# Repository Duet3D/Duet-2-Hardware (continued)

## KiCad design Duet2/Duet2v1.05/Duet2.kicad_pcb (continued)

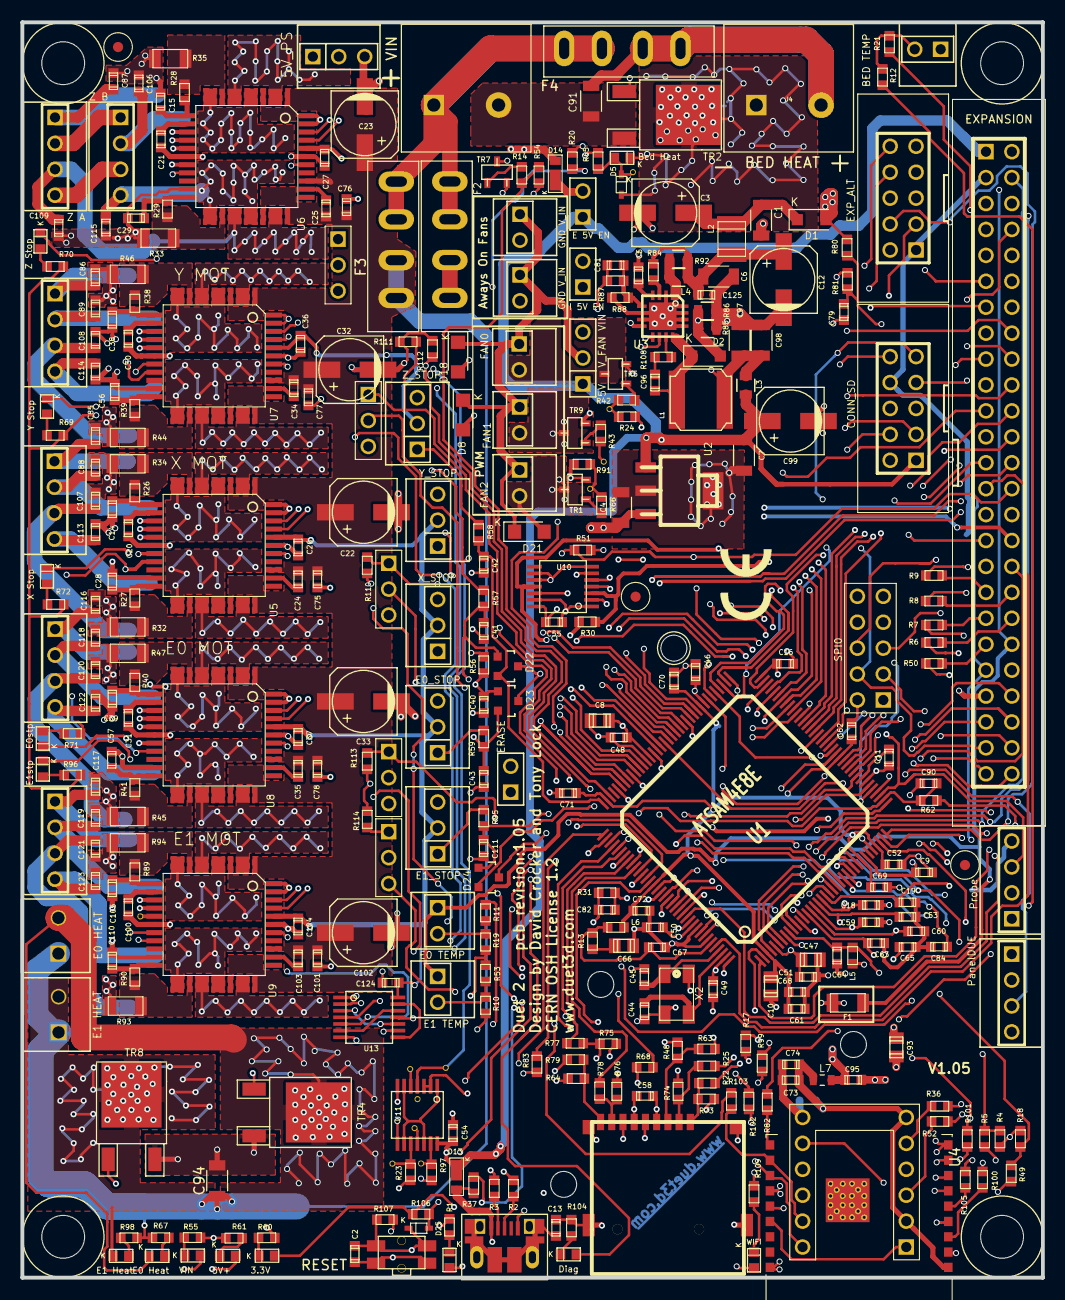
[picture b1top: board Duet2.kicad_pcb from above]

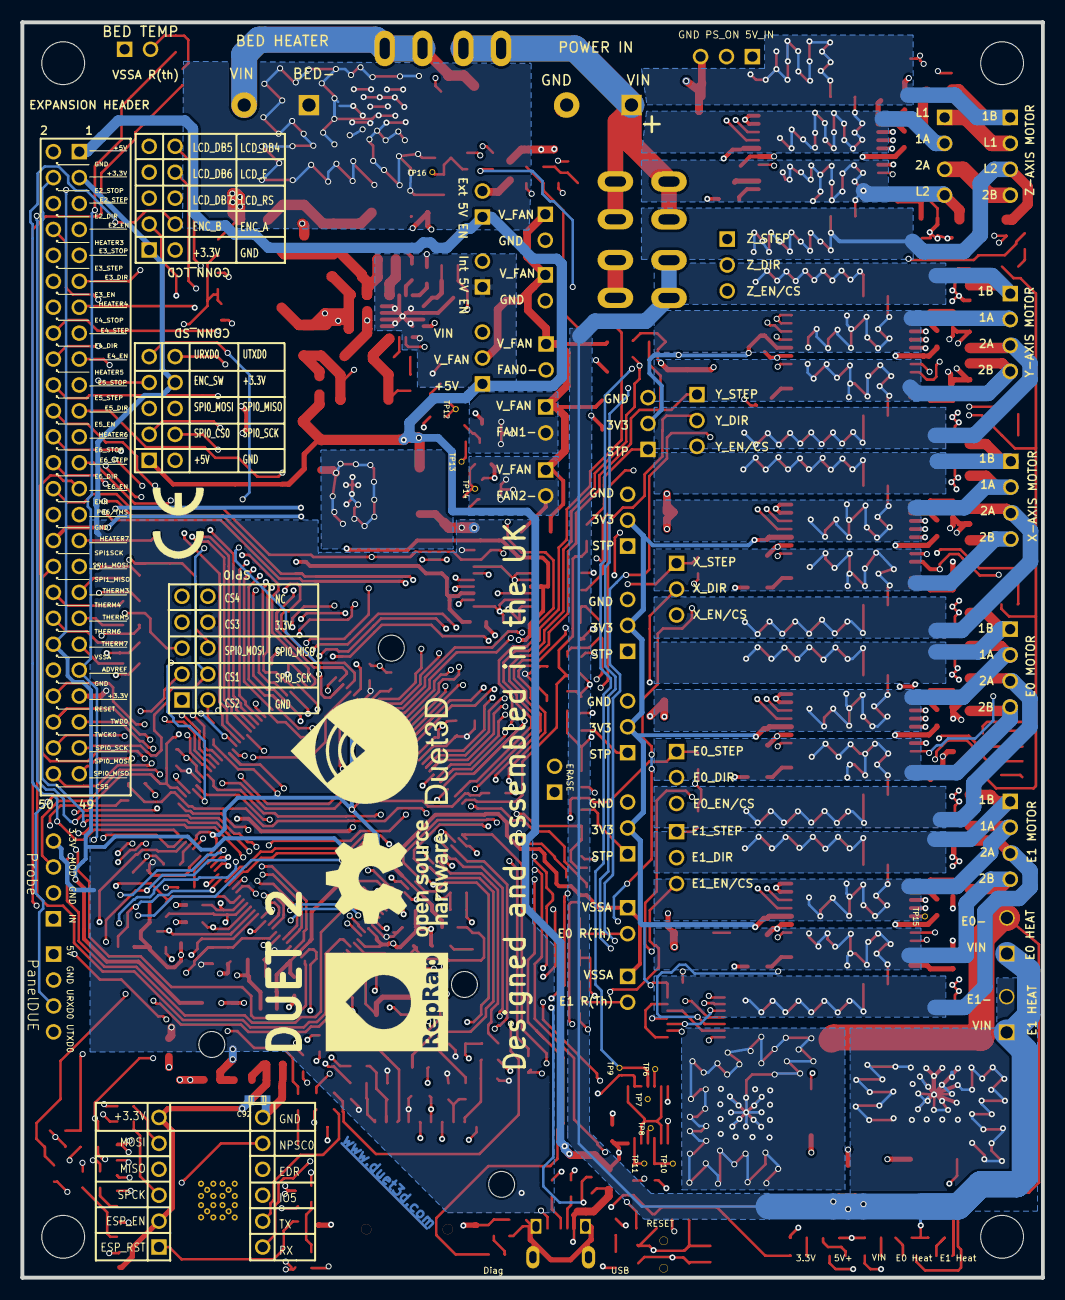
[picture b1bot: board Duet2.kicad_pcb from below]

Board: 4 copper layers, 100.0 x 123.0 mm, 356 parts (5 on the bottom side), 281 nets.

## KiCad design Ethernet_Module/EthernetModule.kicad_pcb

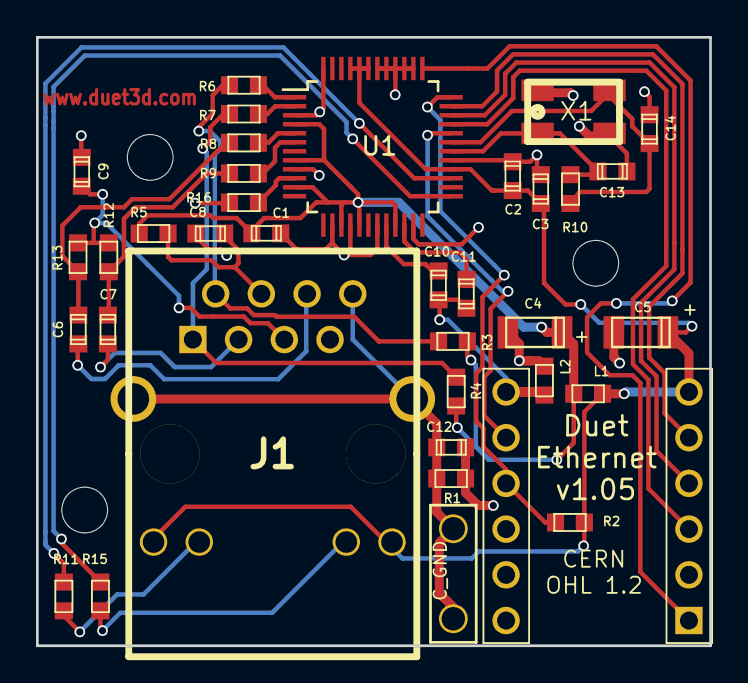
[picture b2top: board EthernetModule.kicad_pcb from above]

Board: 2 copper layers, 37.4 x 33.8 mm, 36 parts (0 on the bottom side), 32 nets.

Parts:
C1, C2, C3: 0u1; C_0603
C4, C5: 10uF/16V; C_1206_pol
C6, C7: 6n8; C_0603
C8: 22n; C_0603
C9, C11: 10n; C_0603
C10: 4u7; C_0603
C12: 0u01 +200V; C_0603
C13, C14: 18p; C_0603
J1: RJ45+MAG
J2: CONN_ALT_HEADER; CONN_ALT_HEADER_th
J3: C_GND; 2.8mm_Spade_terminal
L1, L2: L_MINI; R_0603
R1, R10: 1M; R_0603
R2: 4K7; R_0603
R3, R4, R12, R13: 49R9; R_0603
R5: 10R; R_0603
R6, R7, R8, R9: 33R; R_0603
R11, R15: 220R; R_0603
R16: 12K4; R_0603
U1: W5500; LQFP-48_7x7mm_Pitch0.5mm
X1: CRYSTAL_4PIN; Xtal_5x3.2

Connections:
+3V3: C2.1, C3.1, C5.1, J1.9, J1.12, J2.6, L1.2, R2.2, U1.28, U1.43, U1.44, U1.45
+3V3_A: C1.1, C4.1, L1.1, R3.2, R4.2, R5.2, U1.4, U1.8, U1.11, U1.15, U1.17, U1.21
ACTLED: R11.2, U1.27
AGND: C1.2, C4.2, C8.2, C9.2, L2.1, R16.1, U1.3, U1.9, U1.14, U1.16, U1.19, U1.48
GND: C2.2, C3.2, C5.2, C10.2, C11.2, C12.1, C13.2, C14.2, J2.10, J2.15, L2.2, R1.1, U1.23, U1.29, U1.38, U1.39, U1.40, U1.41, U1.42, X1.2, X1.4
INTn: J2.12, R2.1, U1.36
LINKLED: R15.2, U1.25
MISO: J2.4, U1.34
MOSI: J2.5, U1.35
unnamed: C6.1, R8.1, R13.2
unnamed: C6.2, J1.6
unnamed: C7.1, R9.1, R12.2
unnamed: C7.2, J1.3
unnamed: C8.1, J1.4, R5.1
unnamed: C9.1, J1.5, R12.1, R13.1
unnamed: C10.1, U1.20
unnamed: C11.1, U1.22
unnamed: C12.2, J1.8, J1.13, J1.14, J3.1, R1.2
unnamed: C13.1, R10.2, U1.30, X1.1
unnamed: C14.1, R10.1, U1.31, X1.3
unnamed: J1.1, R4.1, R7.1
unnamed: J1.2, R3.1, R6.1
unnamed: J1.10, R11.1
unnamed: J1.11, R15.1
unnamed: R6.2, U1.1
unnamed: R7.2, U1.2
unnamed: R8.2, U1.5
unnamed: R9.2, U1.6
unnamed: R16.2, U1.10
RSTn: J2.1, U1.37
SCLK: J2.3, U1.33
SCSn: J2.11, U1.32

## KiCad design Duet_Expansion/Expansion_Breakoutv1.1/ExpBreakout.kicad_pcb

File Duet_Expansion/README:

For info on the Duex2/5 see:
https://duet3d.com/wiki/Duex2_and_Duex5_Features

For more info on the Duex4 expansion board see:
http://blog.think3dprint3d.com/2015/04/duex4-v02a-minor-updates.html

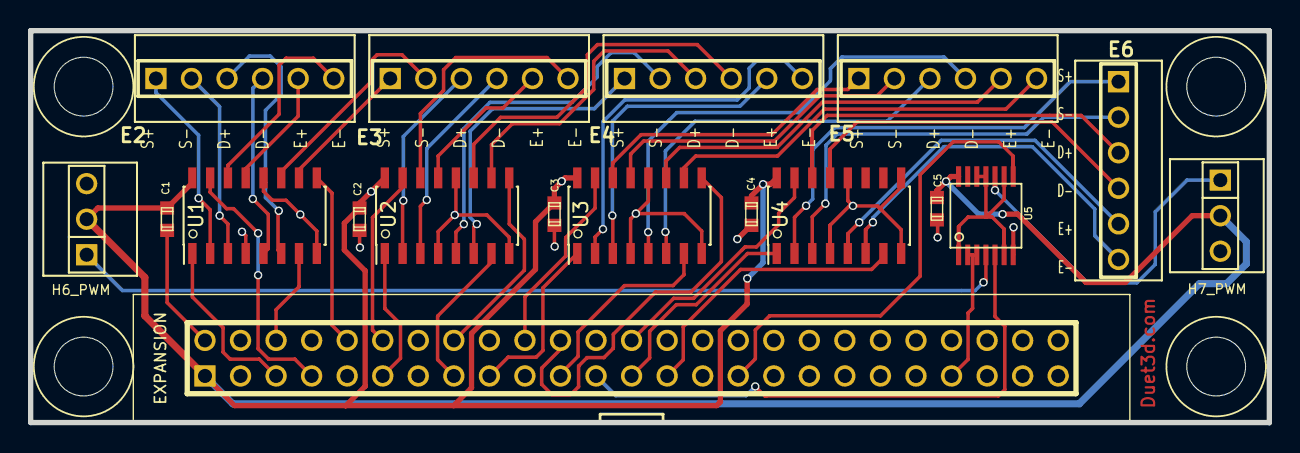
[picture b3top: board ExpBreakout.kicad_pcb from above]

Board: 2 copper layers, 88.5 x 28.0 mm, 22 parts (0 on the bottom side), 53 nets.

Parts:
C1, C2, C3, C4, C5: 0u1; C_0603
J1: EXPANSION; PIN_ARRAY_25X2
M4, M5, M6, M7: MOUNTING; Fixing_M4
P1: E2; PIN_ARRAY_6x1
P2: E3; PIN_ARRAY_6x1
P3: E4; PIN_ARRAY_6x1
P4: E5; PIN_ARRAY_6x1
P5: E6; PIN_ARRAY_6x1
P6: H6_PWM; PIN_ARRAY_3X1
P7: H7_PWM; PIN_ARRAY_3X1
U1, U2, U3, U4: 75ALS192; SOIC-16_3.9x9.9mm_Pitch1.27mm
U5: 74HCT02; TSSOP-14

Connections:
+3.3V: J1.3, J1.43, U5.2, U5.3
+5V: C1.1, C2.1, C3.1, C4.1, C5.1, J1.1, P6.2, P7.2, U1.16, U2.16, U3.16, U4.16, U5.14
E2_DIR: J1.6, U1.7
E2_D_OUT_Y: P1.3, U1.6
E2_D_OUT_Z: P1.4, U1.5
E2_EN: J1.7, U1.15
E2_E_OUT_Y: P1.6, U1.14
E2_E_OUT_Z: P1.5, U1.13
E2_STEP: J1.5, U1.1
E2_S_OUT_Y: P1.1, U1.2
E2_S_OUT_Z: P1.2, U1.3
E3_DIR: J1.11, U2.1
E3_D_OUT_Y: P2.3, U2.2
E3_D_OUT_Z: P2.4, U2.3
E3_EN: J1.12, U2.15
E3_E_OUT_Y: P2.6, U2.14
E3_E_OUT_Z: P2.5, U2.13
E3_STEP: J1.10, U1.9
E3_S_OUT_Y: P2.1, U1.10
E3_S_OUT_Z: P2.2, U1.11
E4_DIR: J1.16, U2.9
E4_D_OUT_Y: P3.3, U2.10
E4_D_OUT_Z: P3.4, U2.11
E4_EN: J1.17, U3.1
E4_E_OUT_Y: P3.6, U3.2
E4_E_OUT_Z: P3.5, U3.3
E4_STEP: J1.15, U2.7
E4_S_OUT_Y: P3.1, U2.6
E4_S_OUT_Z: P3.2, U2.5
E5_DIR: J1.21, U3.7
E5_D_OUT_Y: P4.3, U3.6
E5_D_OUT_Z: P4.4, U3.5
E5_EN: J1.22, U3.9
E5_E_OUT_Y: P4.6, U3.10
E5_E_OUT_Z: P4.5, U3.11
E5_STEP: J1.20, U3.15
E5_S_OUT_Y: P4.1, U3.14
E5_S_OUT_Z: P4.2, U3.13
E6_DIR: J1.26, U4.15
E6_D_OUT_Y: P5.3, U4.14
E6_D_OUT_Z: P5.4, U4.13
E6_EN: J1.27, U4.7
E6_E_OUT_Y: P5.6, U4.6
E6_E_OUT_Z: P5.5, U4.5
E6_STEP: J1.25, U4.1
E6_S_OUT_Y: P5.1, U4.2
E6_S_OUT_Z: P5.2, U4.3
GND: C1.2, C2.2, C3.2, C4.2, C5.2, J1.2, J1.30, J1.42, P6.3, P7.3, U1.4, U1.8, U1.12, U2.4, U2.8, U2.12, U3.4, U3.8, U3.12, U4.4, U4.8, U4.9, U4.12, U5.7
HEATER6: J1.23, U5.5
HEATER6_PWM: P6.1, U5.4
HEATER7: J1.31, U5.8
HEATER7_PWM: P7.1, U5.10
unnamed: U5.1, U5.6, U5.9, U5.11, U5.12

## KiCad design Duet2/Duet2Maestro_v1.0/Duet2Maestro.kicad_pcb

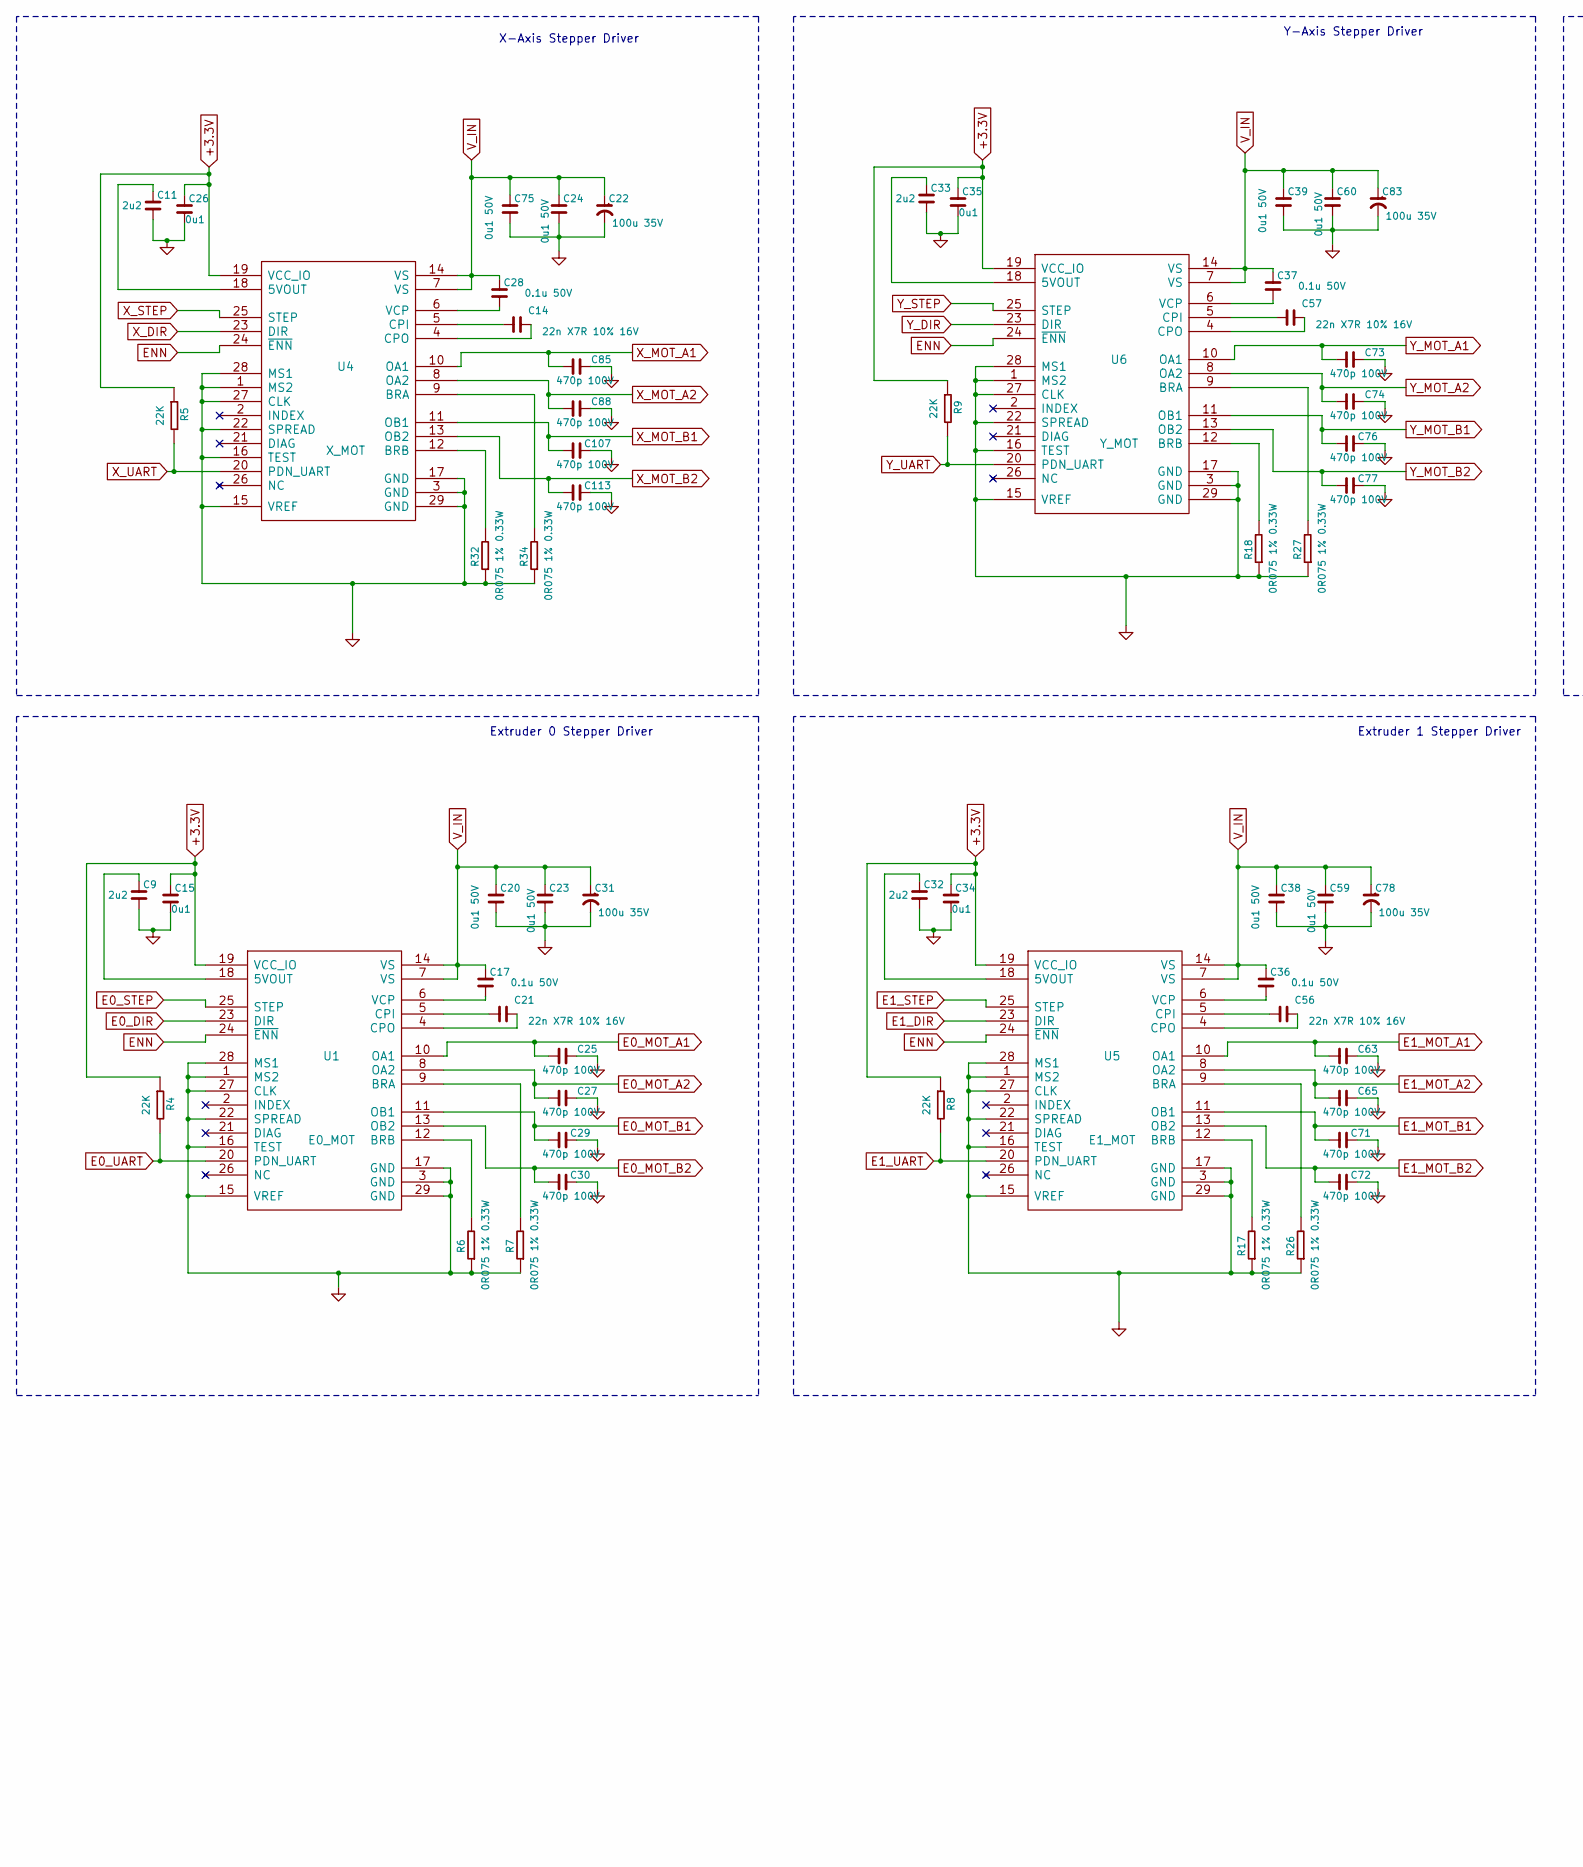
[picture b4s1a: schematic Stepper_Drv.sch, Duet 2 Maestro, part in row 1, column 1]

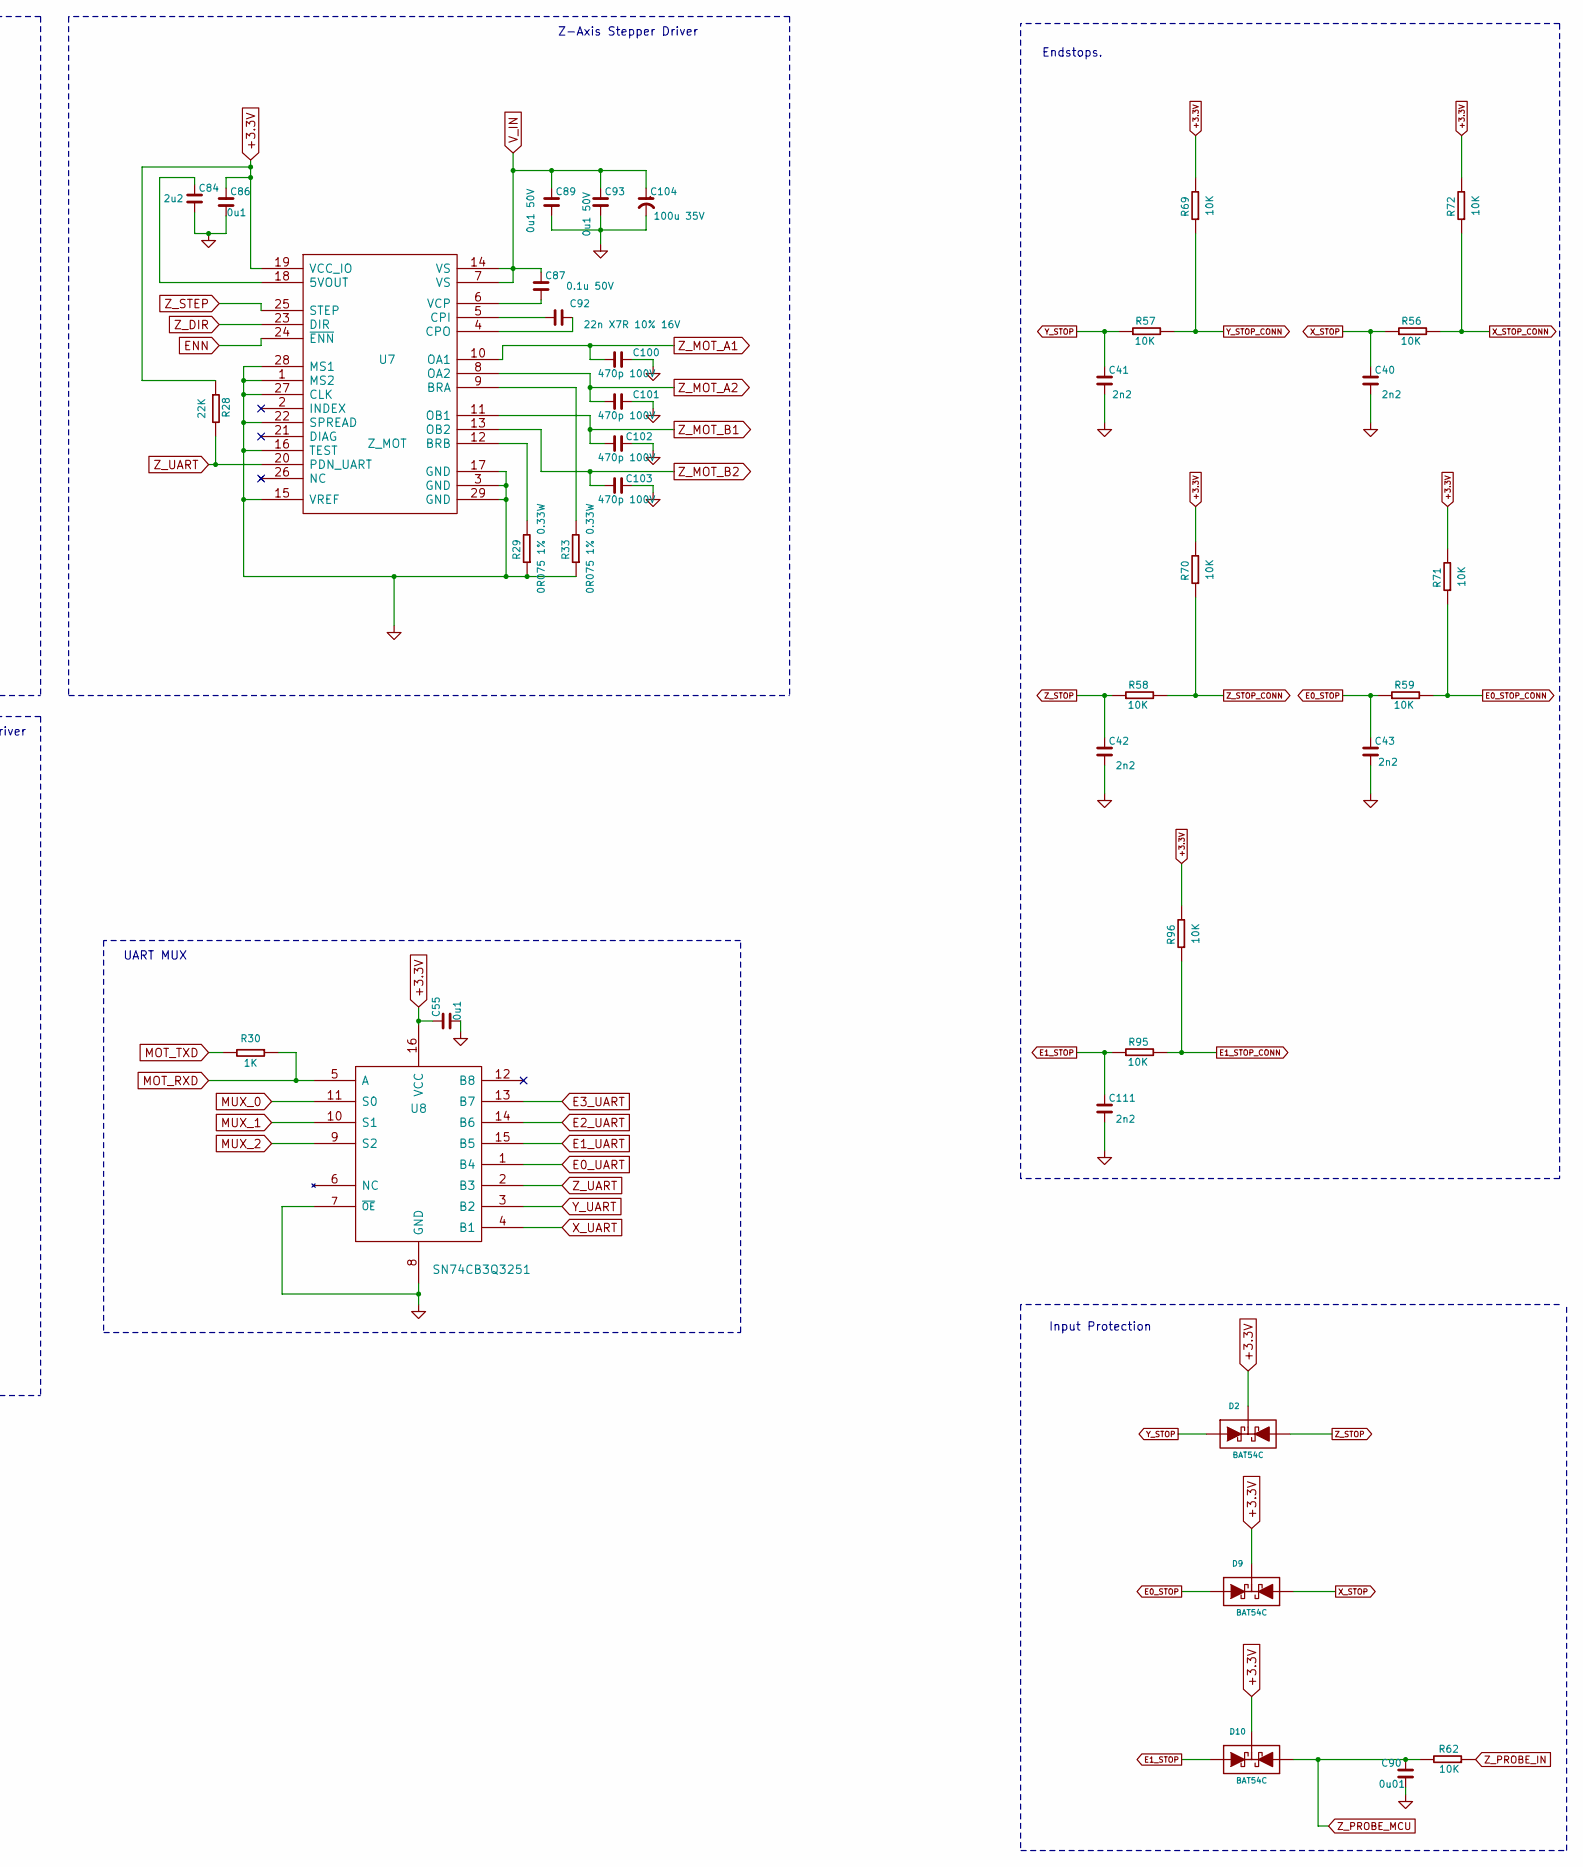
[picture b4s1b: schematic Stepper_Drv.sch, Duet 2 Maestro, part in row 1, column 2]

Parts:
C9, C11, C32, C33, C84: 2u2; C_0603
C14, C21, C56, C57, C92: 22n X7R 10% 16V; C_0603
C15, C26, C34, C35, C55, C86: 0u1; C_0603
C17, C28, C36, C37, C87: 0.1u 50V; C_0603
C20, C23, C24, C38, C39, C59, C60, C75, C89, C93: 0u1 50V; C_0603
C22, C31, C78, C83, C104: 100u 35V; C_ELEC_6.3x7.7
C25, C27, C29, C30, C63, C65, C71, C72, C73, C74, C76, C77, C85, C88, C100, C101, C102, C103, C107, C113: 470p 100V; C_0603
C40, C41, C42, C43, C111: 2n2; C_0603
C90: 0u01; C_0603
D2, D9, D10: BAT54C; SOT-23-D
R4, R5, R8, R9, R28: 22K; R_0603
R6, R7, R17, R18, R26, R27, R29, R32, R33, R34: 0R075 1% 0.33W; R_0603_Large_Pads
R30: 1K; R_0603
R56, R57, R58, R59, R62, R69, R70, R71, R72, R95, R96: 10K; R_0603
U1: E0_MOT; QFN-28-1EP_5x5mm_Pitch0.5mm
U4: X_MOT; QFN-28-1EP_5x5mm_Pitch0.5mm
U5: E1_MOT; QFN-28-1EP_5x5mm_Pitch0.5mm
U6: Y_MOT; QFN-28-1EP_5x5mm_Pitch0.5mm
U7: Z_MOT; QFN-28-1EP_5x5mm_Pitch0.5mm
U8: SN74CB3Q3251; QSOP-16_3.9x4.9mm_Pitch0.635mm

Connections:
+3.3V: C15.1, C26.1, C34.1, C35.1, C55.1, C86.1, D2.3, D9.3, D10.3, R4.1, R5.1, R8.1, R9.1, R28.1, R69.2, R70.2, R71.2, R72.2, R96.2, U1.19 (VCC_IO), U4.19 (VCC_IO), U5.19 (VCC_IO), U6.19 (VCC_IO), U7.19 (VCC_IO), U8.16 (VCC); also elsewhere on the board
E0_DIR: U1.23 (DIR); also elsewhere on the board
E0_MOT_A1: C25.2, U1.10 (OA1); also elsewhere on the board
E0_MOT_A2: C27.2, U1.8 (OA2); also elsewhere on the board
E0_MOT_B1: C29.2, U1.11 (OB1); also elsewhere on the board
E0_MOT_B2: C30.2, U1.13 (OB2); also elsewhere on the board
E0_STEP: U1.25 (STEP); also elsewhere on the board
E0_STOP: C43.1, D9.1, R59.1; also elsewhere on the board
E0_STOP_CONN: R59.2, R71.1; also elsewhere on the board
E0_UART: R4.2, U1.20 (PDN_UART), U8.1 (B4); also elsewhere on the board
E1_DIR: U5.23 (DIR); also elsewhere on the board
E1_MOT_A1: C63.2, U5.10 (OA1); also elsewhere on the board
E1_MOT_A2: C65.2, U5.8 (OA2); also elsewhere on the board
E1_MOT_B1: C71.2, U5.11 (OB1); also elsewhere on the board
E1_MOT_B2: C72.2, U5.13 (OB2); also elsewhere on the board
E1_STEP: U5.25 (STEP); also elsewhere on the board
E1_STOP: C111.1, D10.1, R95.1; also elsewhere on the board
E1_STOP_CONN: R95.2, R96.1; also elsewhere on the board
E1_UART: R8.2, U5.20 (PDN_UART), U8.15 (B5); also elsewhere on the board
E2_UART: U8.14 (B6); also elsewhere on the board
E3_UART: U8.13 (B7); also elsewhere on the board
ENN: U1.24 (~ENN), U4.24 (~ENN), U5.24 (~ENN), U6.24 (~ENN), U7.24 (~ENN); also elsewhere on the board
GND: C9.2, C11.2, C15.2, C20.2, C22.2, C23.2, C24.2, C25.1, C26.2, C27.1, C29.1, C30.1, C31.2, C32.2, C33.2, C34.2, C35.2, C38.2, C39.2, C40.2, C41.2, C42.2, C43.2, C55.2, C59.2, C60.2, C63.1, C65.1, C71.1, C72.1, C73.1, C74.1, C75.2, C76.1, C77.1, C78.2, C83.2, C84.2, C85.1, C86.2, C88.1, C89.2, C90.2, C93.2, C100.1, C101.1, C102.1, C103.1, C104.2, C107.1, C111.2, C113.1, R6.1, R7.1, R17.1, R18.1, R26.1, R27.1, R29.1, R32.1, R33.1, R34.1, U1.1 (MS2), U1.3 (GND), U1.15 (VREF), U1.16 (TEST), U1.17 (GND), U1.22 (SPREAD), U1.27 (CLK), U1.28 (MS1), U1.29 (GND), U4.1 (MS2), U4.3 (GND), U4.15 (VREF), U4.16 (TEST), U4.17 (GND), U4.22 (SPREAD), U4.27 (CLK), U4.28 (MS1), U4.29 (GND), U5.1 (MS2), U5.3 (GND), U5.15 (VREF), U5.16 (TEST), U5.17 (GND), U5.22 (SPREAD), U5.27 (CLK), U5.28 (MS1), U5.29 (GND), U6.1 (MS2), U6.3 (GND), U6.15 (VREF), U6.16 (TEST), U6.17 (GND), U6.22 (SPREAD), U6.27 (CLK), U6.28 (MS1), U6.29 (GND), U7.1 (MS2), U7.3 (GND), U7.15 (VREF), U7.16 (TEST), U7.17 (GND), U7.22 (SPREAD), U7.27 (CLK), U7.28 (MS1), U7.29 (GND), U8.7 (~OE), U8.8 (GND); also elsewhere on the board
MOT_RXD: R30.1, U8.5 (A); also elsewhere on the board
MOT_TXD: R30.2; also elsewhere on the board
MUX_0: U8.11 (S0); also elsewhere on the board
MUX_1: U8.10 (S1); also elsewhere on the board
MUX_2: U8.9 (S2); also elsewhere on the board
unnamed: C9.1, U1.18 (5VOUT)
unnamed: C11.1, U4.18 (5VOUT)
unnamed: C14.1, U4.4 (CPO)
unnamed: C14.2, U4.5 (CPI)
unnamed: C17.2, U1.6 (VCP)
unnamed: C21.1, U1.4 (CPO)
unnamed: C21.2, U1.5 (CPI)
unnamed: C28.2, U4.6 (VCP)
unnamed: C32.1, U5.18 (5VOUT)
unnamed: C33.1, U6.18 (5VOUT)
unnamed: C36.2, U5.6 (VCP)
unnamed: C37.2, U6.6 (VCP)
unnamed: C56.1, U5.4 (CPO)
unnamed: C56.2, U5.5 (CPI)
unnamed: C57.1, U6.4 (CPO)
unnamed: C57.2, U6.5 (CPI)
unnamed: C84.1, U7.18 (5VOUT)
unnamed: C87.2, U7.6 (VCP)
unnamed: C92.1, U7.4 (CPO)
unnamed: C92.2, U7.5 (CPI)
unnamed: R6.2, U1.12 (BRB)
unnamed: R7.2, U1.9 (BRA)
unnamed: R17.2, U5.12 (BRB)
unnamed: R18.2, U6.12 (BRB)
unnamed: R26.2, U5.9 (BRA)
unnamed: R27.2, U6.9 (BRA)
unnamed: R29.2, U7.12 (BRB)
unnamed: R32.2, U4.12 (BRB)
unnamed: R33.2, U7.9 (BRA)
unnamed: R34.2, U4.9 (BRA)
V_IN: C17.1, C20.1, C22.1, C23.1, C24.1, C28.1, C31.1, C36.1, C37.1, C38.1, C39.1, C59.1, C60.1, C75.1, C78.1, C83.1, C87.1, C89.1, C93.1, C104.1, U1.7 (VS), U1.14 (VS), U4.7 (VS), U4.14 (VS), U5.7 (VS), U5.14 (VS), U6.7 (VS), U6.14 (VS), U7.7 (VS), U7.14 (VS); also elsewhere on the board
X_DIR: U4.23 (DIR); also elsewhere on the board
X_MOT_A1: C85.2, U4.10 (OA1); also elsewhere on the board
X_MOT_A2: C88.2, U4.8 (OA2); also elsewhere on the board
X_MOT_B1: C107.2, U4.11 (OB1); also elsewhere on the board
X_MOT_B2: C113.2, U4.13 (OB2); also elsewhere on the board
X_STEP: U4.25 (STEP); also elsewhere on the board
X_STOP: C40.1, D9.2, R56.1; also elsewhere on the board
X_STOP_CONN: R56.2, R72.1; also elsewhere on the board
X_UART: R5.2, U4.20 (PDN_UART), U8.4 (B1); also elsewhere on the board
Y_DIR: U6.23 (DIR); also elsewhere on the board
Y_MOT_A1: C73.2, U6.10 (OA1); also elsewhere on the board
Y_MOT_A2: C74.2, U6.8 (OA2); also elsewhere on the board
Y_MOT_B1: C76.2, U6.11 (OB1); also elsewhere on the board
Y_MOT_B2: C77.2, U6.13 (OB2); also elsewhere on the board
Y_STEP: U6.25 (STEP); also elsewhere on the board
Y_STOP: C41.1, D2.1, R57.1; also elsewhere on the board
Y_STOP_CONN: R57.2, R69.1; also elsewhere on the board
Y_UART: R9.2, U6.20 (PDN_UART), U8.3 (B2); also elsewhere on the board
Z_DIR: U7.23 (DIR); also elsewhere on the board
Z_MOT_A1: C100.2, U7.10 (OA1); also elsewhere on the board
Z_MOT_A2: C101.2, U7.8 (OA2); also elsewhere on the board
Z_MOT_B1: C102.2, U7.11 (OB1); also elsewhere on the board
Z_MOT_B2: C103.2, U7.13 (OB2); also elsewhere on the board
Z_PROBE_IN: R62.1; also elsewhere on the board
Z_PROBE_MCU: C90.1, D10.2, R62.2; also elsewhere on the board
Z_STEP: U7.25 (STEP); also elsewhere on the board
Z_STOP: C42.1, D2.2, R58.1; also elsewhere on the board
Z_STOP_CONN: R58.2, R70.1; also elsewhere on the board
Z_UART: R28.2, U7.20 (PDN_UART), U8.2 (B3); also elsewhere on the board

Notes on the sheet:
Endstops.
Extruder 0 Stepper Driver
Y-Axis Stepper Driver
X-Axis Stepper Driver
Extruder 1 Stepper Driver
UART MUX
Z-Axis Stepper Driver
Input Protection

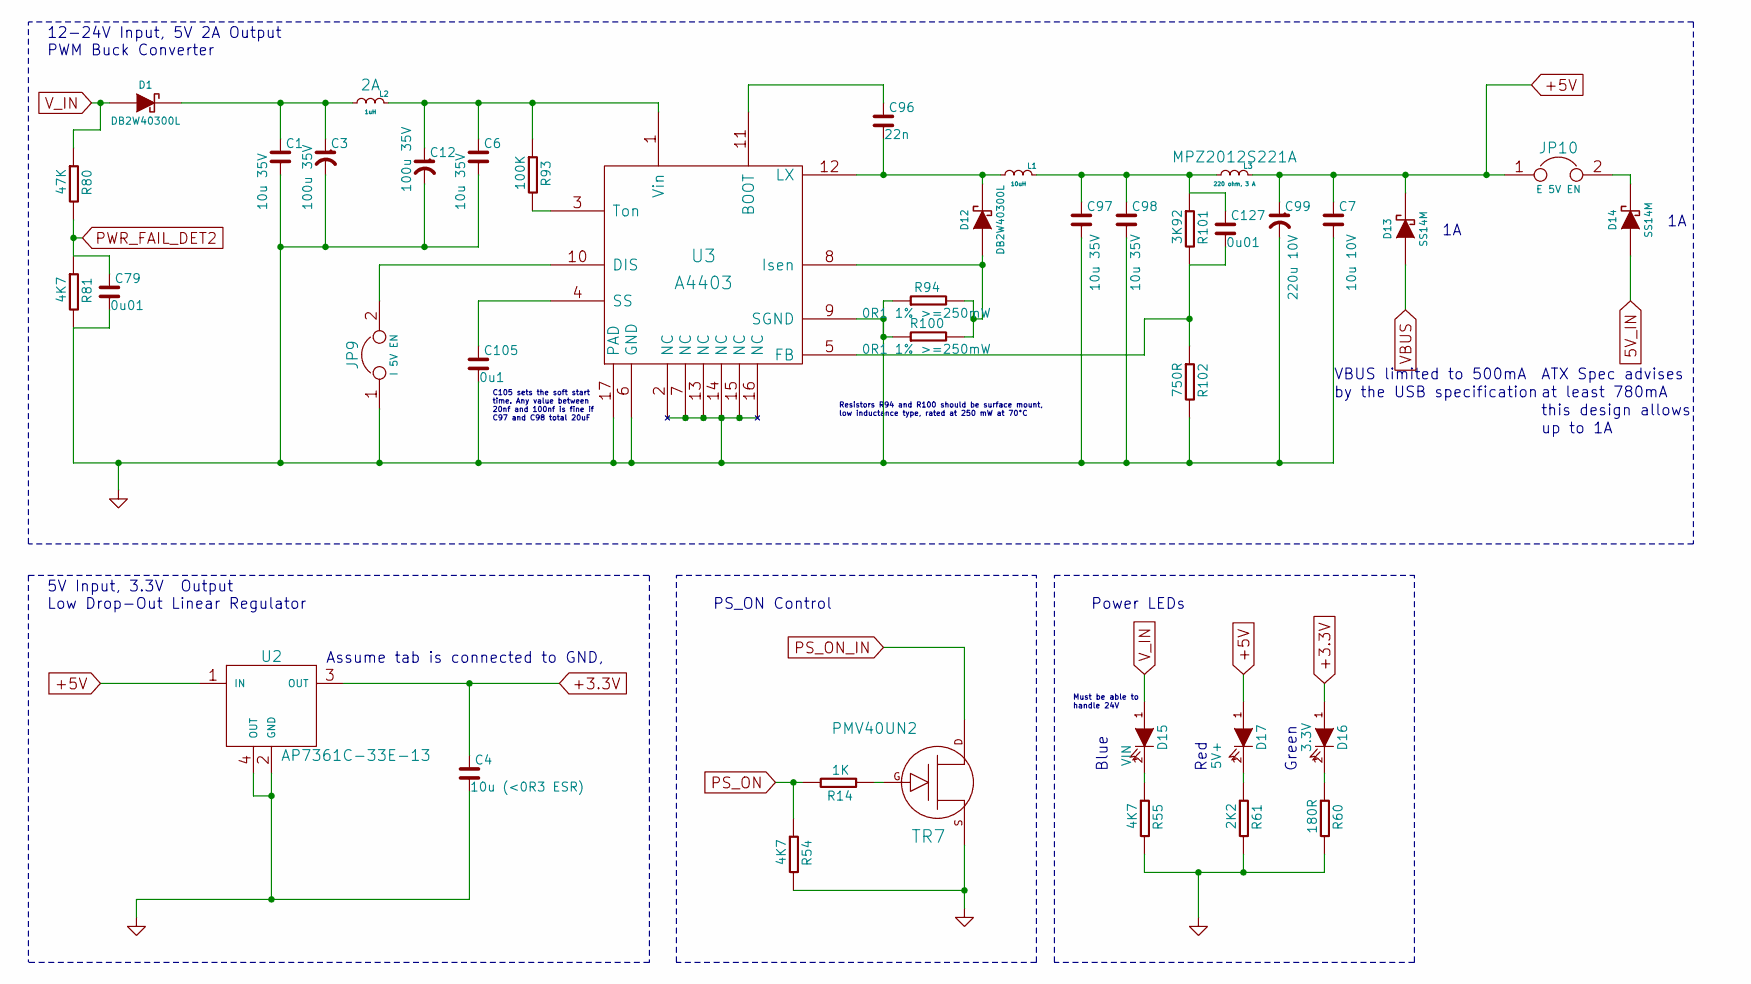
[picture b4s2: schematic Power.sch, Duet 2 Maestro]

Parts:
C1, C6, C97, C98: 10u 35V; C_1206
C3, C12: 100u 35V; C_ELEC_6.3x7.7
C4: 10u (<0R3 ESR); C_0805
C7: 10u 10V; C_0805
C79, C127: 0u01; C_0603
C96: 22n; C_0603
C99: 220u 10V; C_ELEC_6.3x7.7
C105: 0u1; C_0603
D1, D12: DB2W40300L; D_SOD-123F
D13, D14: SS14M; uSMA
D15: VIN; D_0603
D16: 3.3V; D_0603
D17: 5V+; D_0603
JP9: I 5V EN; JUMPER
JP10: E 5V EN; JUMPER
L1: 10uH; L_6x6
L2: 1uH; C_1210; Rating 2A
L3: 220 ohm, 3 A; R_0805; Rating MPZ2012S221A
R14: 1K; R_0603
R54, R55, R81: 4K7; R_0603
R60: 180R; R_0603
R61: 2K2; R_0603
R80: 47K; R_0603
R93: 100K; R_0603
R94, R100: 0R1 1% >=250mW; R_1206
R101: 3K92; R_0603
R102: 750R; R_0603
TR7: PMV40UN2; SOT-23
U2: AP7361C-33E-13; SOT-223
U3: A4403; QFN16-4x4

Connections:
5V_IN: D14.1 (A); also elsewhere on the board
+3.3V: C4.1, D16.1 (A), U2.3 (OUT); also elsewhere on the board
+5V: C7.1, C99.1, D13.2 (K), D17.1 (A), JP10.1, L3.1 (A), U2.1 (IN); also elsewhere on the board
GND: C1.2, C3.2, C4.2, C6.2, C7.2, C12.2, C79.2, C97.2, C98.2, C99.2, C105.2, JP9.1, R54.2, R55.2, R60.2, R61.2, R81.2, R94.1, R100.1, R102.2, TR7.S, U2.2 (GND), U2.4 (OUT), U3.2 (NC), U3.6 (GND), U3.7 (NC), U3.9 (SGND), U3.13 (NC), U3.14 (NC), U3.15 (NC), U3.16 (NC), U3.17 (PAD); also elsewhere on the board
unnamed: C1.1, C3.1, D1.1 (K), L2.2 (B)
unnamed: C6.1, C12.1, L2.1 (A), R93.1, U3.1 (Vin)
unnamed: C96.1, U3.11 (BOOT)
unnamed: C96.2, D12.1 (K), L1.2 (B), U3.12 (LX)
unnamed: C105.1, U3.4 (SS)
unnamed: C97.1, C98.1, C127.1, L1.1 (A), L3.2 (B), R101.1
unnamed: C127.2, R101.2, R102.1, U3.5 (FB)
unnamed: D12.2 (A), R94.2, R100.2, U3.8 (Isen)
unnamed: D14.2 (K), JP10.2
unnamed: D15.2 (K), R55.1
unnamed: D16.2 (K), R60.1
unnamed: D17.2 (K), R61.1
unnamed: JP9.2, U3.10 (DIS)
unnamed: R14.1, TR7.G
unnamed: R93.2, U3.3 (Ton)
PS_ON: R14.2, R54.1; also elsewhere on the board
PS_ON_IN: TR7.D; also elsewhere on the board
PWR_FAIL_DET2: C79.1, R80.2, R81.1; also elsewhere on the board
VBUS: D13.1 (A); also elsewhere on the board
V_IN: D1.2 (A), D15.1 (A), R80.1; also elsewhere on the board

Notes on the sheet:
PS_ON Control
5V Input, 3.3V Output Low Drop-Out Linear Regulator
Power LEDs
Must be able to handle 24V
Blue
Red
Green
Assume tab is connected to GND,
up to 1A
this design allows
at least 780mA
ATX Spec advises
by the USB specification
VBUS limited to 500mA
12-24V Input, 5V 2A Output PWM Buck Converter
Resistors R94 and R100 should be surface mount, low inductance type, rated at 250 mW at 70°C
C105 sets the soft start time. Any value between 20nf and 100nf is fine if C97 and C98 total 20uF
